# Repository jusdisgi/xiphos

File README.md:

# Slim Splaydy

This is the real Slim Splaydy. All the other Slim Splaydies are just imitating...

It's a 34-key split ergo layout with a bit of splay and quite a bit of stagger, using Kailh PG1316S ultra-low-profile switches. The result should be extemely slim. I'm using a nice!nano controller, SMD to the board upside down with a cutout for the components, so it chould only be 1.6mm above the PCB surface. The PCB is also cut away where the battery goes, and the case includes a battery holder, allowing up to a 3.0mm battery. The case also has holes for magnets to sit just below the surface, allowing the two sides to magnetically clasp together for transport. When closed up this way the two halves should come in around 8mm thick.

The design is intended to be very easy to assemble. Fvery component on the board is SMD, and all are on the front side. So it should be buildable in one run on a hot plate. Should not even need a soldering iron!

This repo includes the ergogen config file, kicad PCB and schematic files for both left and right halves, and STEP files of all case pieces. Production files and a build guide will follow once everything is finalized.

Here are some pictures...

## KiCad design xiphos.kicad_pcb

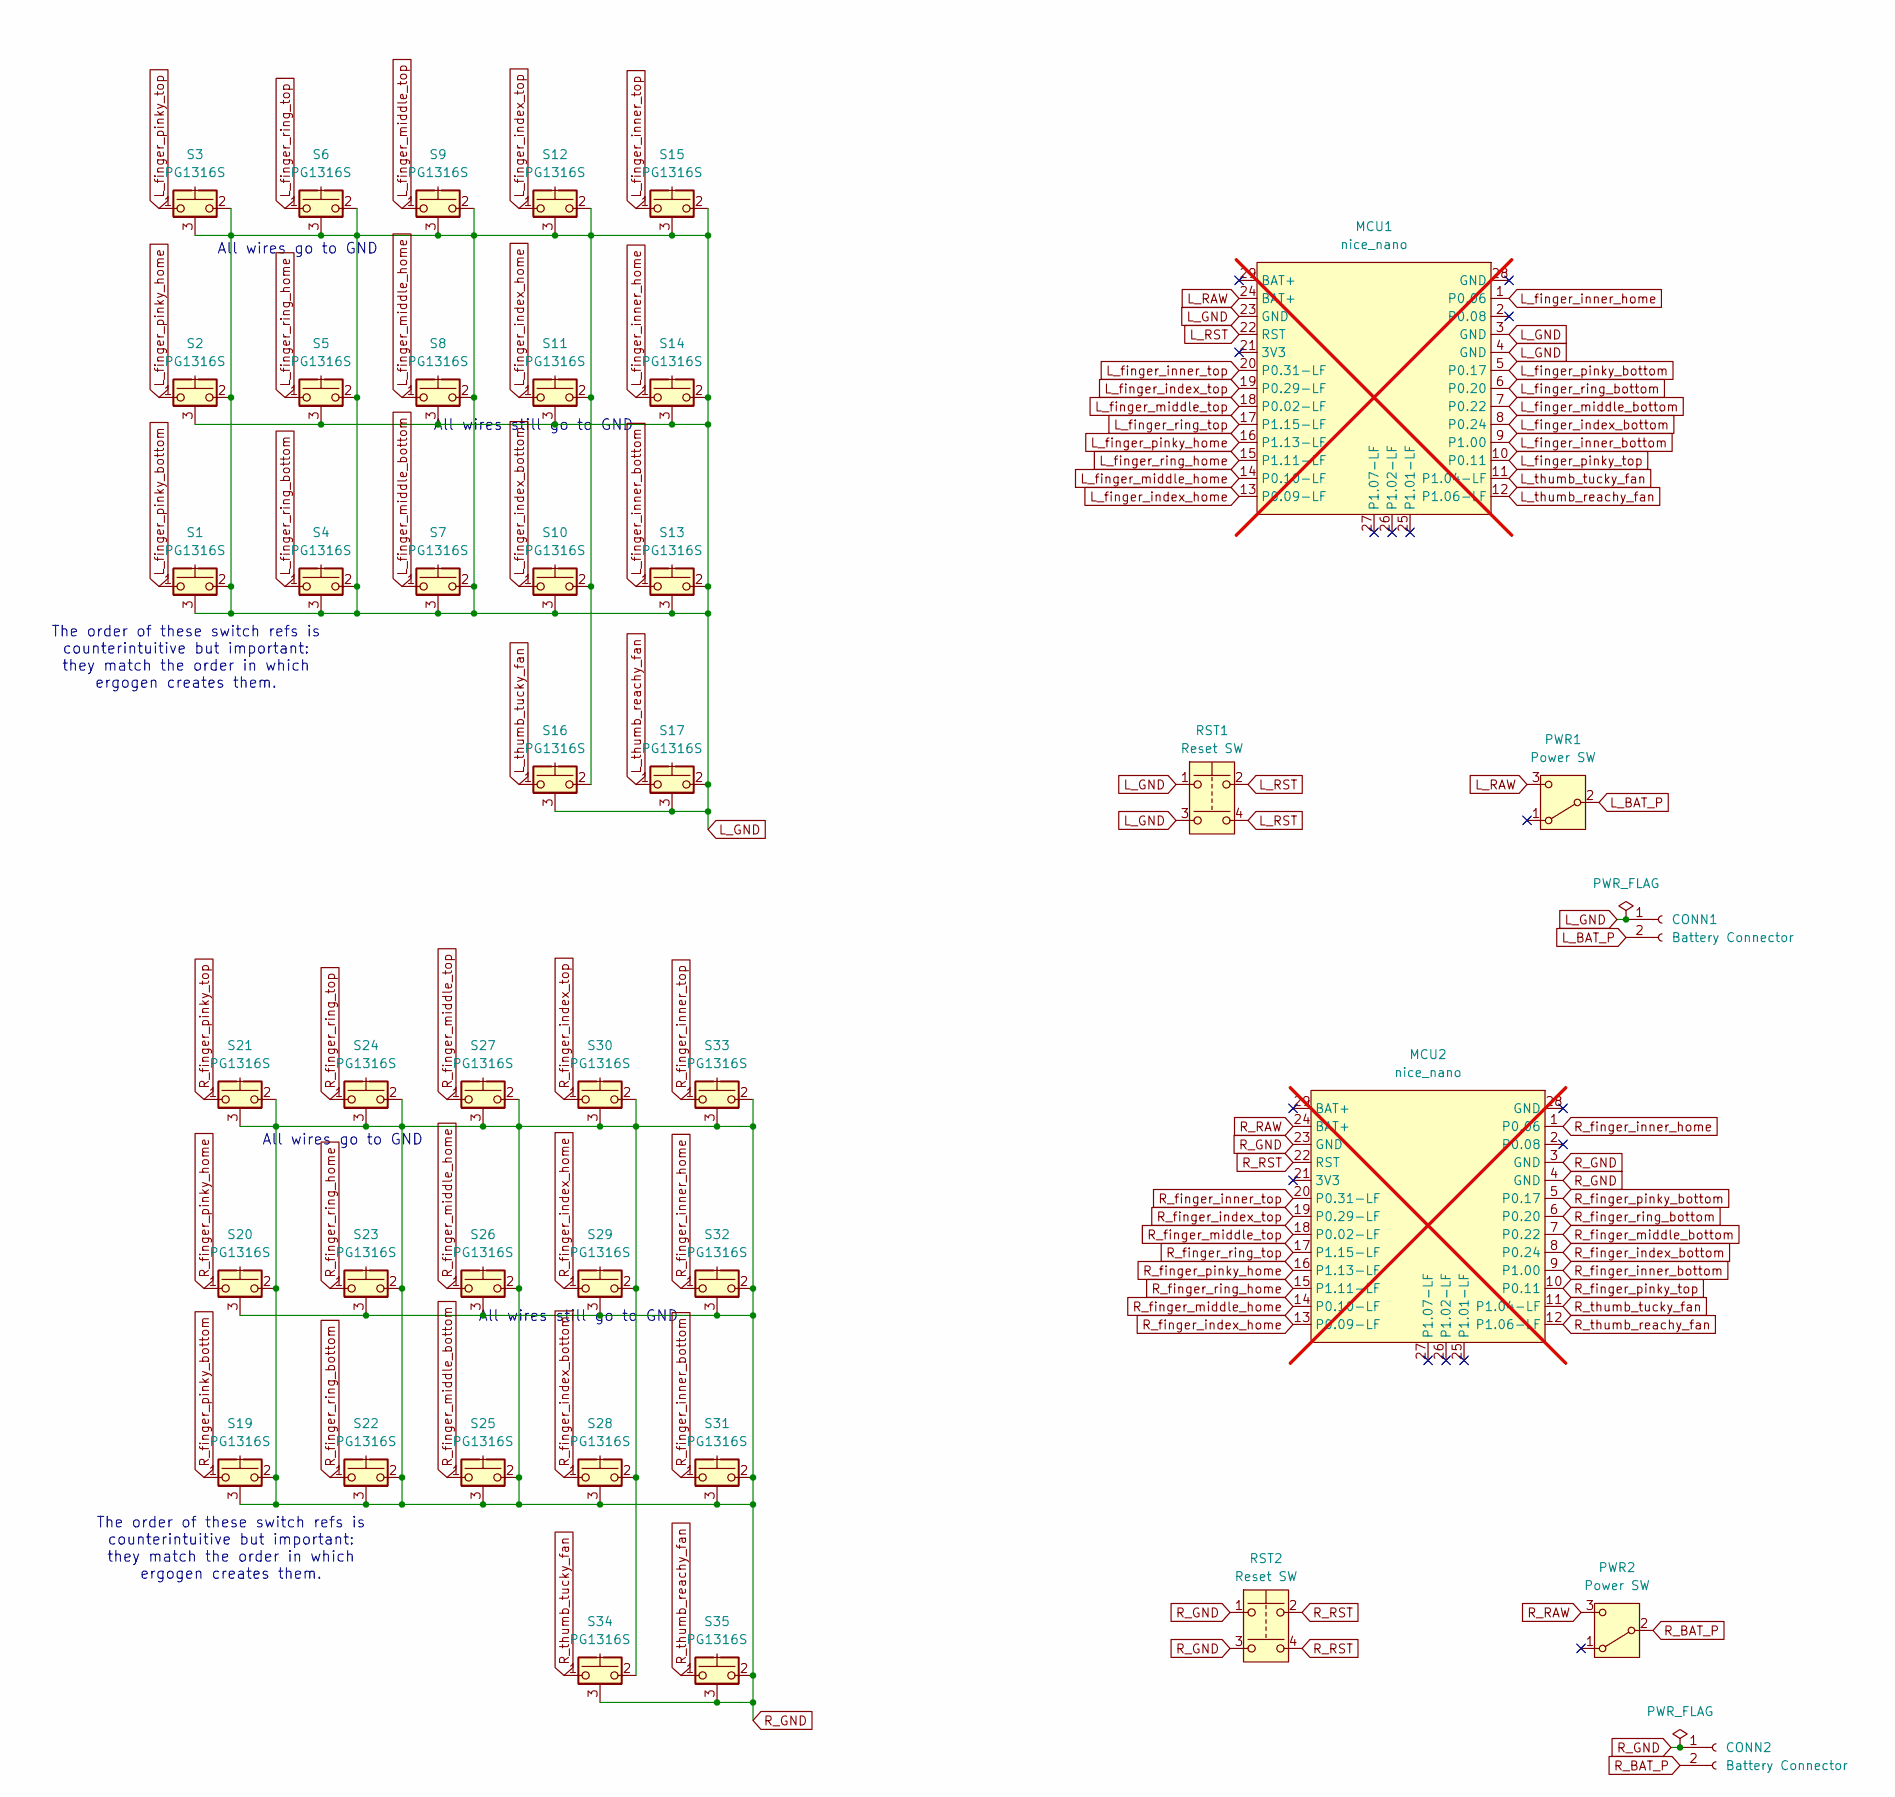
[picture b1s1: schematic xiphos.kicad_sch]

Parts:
CONN1, CONN2: Battery Connector; Molex_Pico-EZmate_78171-0002_1x02-1MP_P1.20mm_Vertical; LCSC C505023
MCU1, MCU2: nice_nano; nice_nano_AH_USBup; LCSC DNP; not fitted
PWR1, PWR2: Power SW; power_switch_smd_side; LCSC C2911519
RST1, RST2: Reset SW; reset_switch_smd_side; LCSC C79174
S1, S2, S3, S4, S5, S6, S7, S8, S9, S10, S11, S12, S13, S14, S15, S16, S17, S19, S20, S21, S22, S23, S24, S25, S26, S27, S28, S29, S30, S31, S32, S33, S34, S35: PG1316S; LCSC C9900170245

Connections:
L_3V3: MCU1.21 (3V3)
L_BAT_P: CONN1.2, PWR1.2 (B)
L_GND: CONN1.1, MCU1.3 (GND), MCU1.4 (GND), MCU1.23 (GND), RST1.1, RST1.3, S1.2, S1.3 (B), S2.2, S2.3 (B), S3.2, S3.3 (B), S4.2, S4.3 (B), S5.2, S5.3 (B), S6.2, S6.3 (B), S7.2, S7.3 (B), S8.2, S8.3 (B), S9.2, S9.3 (B), S10.2, S10.3 (B), S11.2, S11.3 (B), S12.2, S12.3 (B), S13.2, S13.3 (B), S14.2, S14.3 (B), S15.2, S15.3 (B), S16.2, S16.3 (B), S17.2, S17.3 (B); also elsewhere on the board
L_RAW: MCU1.24 (BAT+), PWR1.3 (C)
L_RST: MCU1.22 (RST), RST1.2, RST1.4
L_finger_index_bottom: MCU1.8 (P0.24), S10.1
L_finger_index_home: MCU1.13 (P0.09-LF), S11.1
L_finger_index_top: MCU1.19 (P0.29-LF), S12.1
L_finger_inner_bottom: MCU1.9 (P1.00), S13.1
L_finger_inner_home: MCU1.1 (P0.06), S14.1
L_finger_inner_top: MCU1.20 (P0.31-LF), S15.1
L_finger_middle_bottom: MCU1.7 (P0.22), S7.1
L_finger_middle_home: MCU1.14 (P0.10-LF), S8.1
L_finger_middle_top: MCU1.18 (P0.02-LF), S9.1
L_finger_pinky_bottom: MCU1.5 (P0.17), S1.1
L_finger_pinky_home: MCU1.16 (P1.13-LF), S2.1
L_finger_pinky_top: MCU1.10 (P0.11), S3.1
L_finger_ring_bottom: MCU1.6 (P0.20), S4.1
L_finger_ring_home: MCU1.15 (P1.11-LF), S5.1
L_finger_ring_top: MCU1.17 (P1.15-LF), S6.1
L_shift_outer_mid: MCU1.2 (P0.08); also elsewhere on the board
L_thumb_reachy_fan: MCU1.12 (P1.06-LF), S17.1
L_thumb_tucky_fan: MCU1.11 (P1.04-LF), S16.1
R_3V3: MCU2.21 (3V3)
R_BAT_P: CONN2.2, PWR2.2 (B)
R_GND: CONN2.1, MCU2.3 (GND), MCU2.4 (GND), MCU2.23 (GND), RST2.1, RST2.3, S19.2, S19.3 (B), S20.2, S20.3 (B), S21.2, S21.3 (B), S22.2, S22.3 (B), S23.2, S23.3 (B), S24.2, S24.3 (B), S25.2, S25.3 (B), S26.2, S26.3 (B), S27.2, S27.3 (B), S28.2, S28.3 (B), S29.2, S29.3 (B), S30.2, S30.3 (B), S31.2, S31.3 (B), S32.2, S32.3 (B), S33.2, S33.3 (B), S34.2, S34.3 (B), S35.2, S35.3 (B); also elsewhere on the board
R_RAW: MCU2.24 (BAT+), PWR2.1 (A), PWR2.3 (C)
R_RST: MCU2.22 (RST), RST2.2, RST2.4
R_finger_index_bottom: MCU2.8 (P0.24), S28.1
R_finger_index_home: MCU2.13 (P0.09-LF), S29.1
R_finger_index_top: MCU2.19 (P0.29-LF), S30.1
R_finger_inner_bottom: MCU2.9 (P1.00), S31.1
R_finger_inner_home: MCU2.1 (P0.06), S32.1
R_finger_inner_top: MCU2.20 (P0.31-LF), S33.1
R_finger_middle_bottom: MCU2.7 (P0.22), S25.1
R_finger_middle_home: MCU2.14 (P0.10-LF), S26.1
R_finger_middle_top: MCU2.18 (P0.02-LF), S27.1
R_finger_pinky_bottom: MCU2.5 (P0.17), S19.1
R_finger_pinky_home: MCU2.16 (P1.13-LF), S20.1
R_finger_pinky_top: MCU2.10 (P0.11), S21.1
R_finger_ring_bottom: MCU2.6 (P0.20), S22.1
R_finger_ring_home: MCU2.15 (P1.11-LF), S23.1
R_finger_ring_top: MCU2.17 (P1.15-LF), S24.1
R_shift_outer_mid: MCU2.2 (P0.08); also elsewhere on the board
R_thumb_reachy_fan: MCU2.12 (P1.06-LF), S35.1
R_thumb_tucky_fan: MCU2.11 (P1.04-LF), S34.1

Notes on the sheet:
All wires still go to GND
The order of these switch refs is counterintuitive but important: they match the order in which ergogen creates them.
All wires go to GND

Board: 2 copper layers, 76 parts (2 on the bottom side), 44 nets, no tracks yet.

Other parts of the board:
MAG1, MAG2: magsafe
MH1, MH2, MH3, MH4, MH5, MH6, MH7, MH8, MH9, MH10, MH11, MH12, MH13, MH14, MH15, MH16, MH17, MH18, MH19, MH20, MH21, MH22, MH23, MH24, MH25, MH26, MH27, MH28, MH29, MH30: mounting_hole_npth
S18, S36: PG1316S

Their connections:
L_GND: S18.2, S18.3; also elsewhere on the board
L_shift_outer_mid: S18.1; also elsewhere on the board
R_GND: S36.2, S36.3; also elsewhere on the board
R_shift_outer_mid: S36.1; also elsewhere on the board

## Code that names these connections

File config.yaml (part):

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            P1_label: D1
            P0: L_shift_outer_mid
            P0_label: D0
            P2: L_finger_pinky_bottom
            P2_label: D2
            P3: L_finger_ring_bottom
            P3_label: D3
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            P5_label: D5
            P6: L_finger_inner_bottom
            P6_label: D6
            P7: L_finger_pinky_top
            P7_label: D7
            P8: L_thumb_tucky_fan
            P8_label: D8
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            P16_label: D16
            P14: L_finger_ring_home
            P14_label: D14
            P15: L_finger_pinky_home
            P15_label: D15
            P18: L_finger_ring_top
            P18_label: D18
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            P1_label: D1
            P0: R_shift_outer_mid
            P0_label: D0
            P2: R_finger_pinky_bottom
            P2_label: D2
            P3: R_finger_ring_bottom
            P3_label: D3
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            P5_label: D5
            P6: R_finger_inner_bottom
            P6_label: D6
            P7: R_finger_pinky_top
            P7_label: D7
            P8: R_thumb_tucky_fan
            P8_label: D8
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            P16_label: D16
            P14: R_finger_ring_home
            P14_label: D14
            P15: R_finger_pinky_home
            P15_label: D15
            P18: R_finger_ring_top
            P18_label: D18
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
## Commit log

2026-06-04 Initial commit.
2026-06-04 Initial Commit, The Sequel
2026-06-04 Create new Xiphos design
2026-06-05 cleanup
2026-06-06 Adjust magsafe position
2026-06-18 Create new outline and mounting holes. Cleanup. Ready for routing.
